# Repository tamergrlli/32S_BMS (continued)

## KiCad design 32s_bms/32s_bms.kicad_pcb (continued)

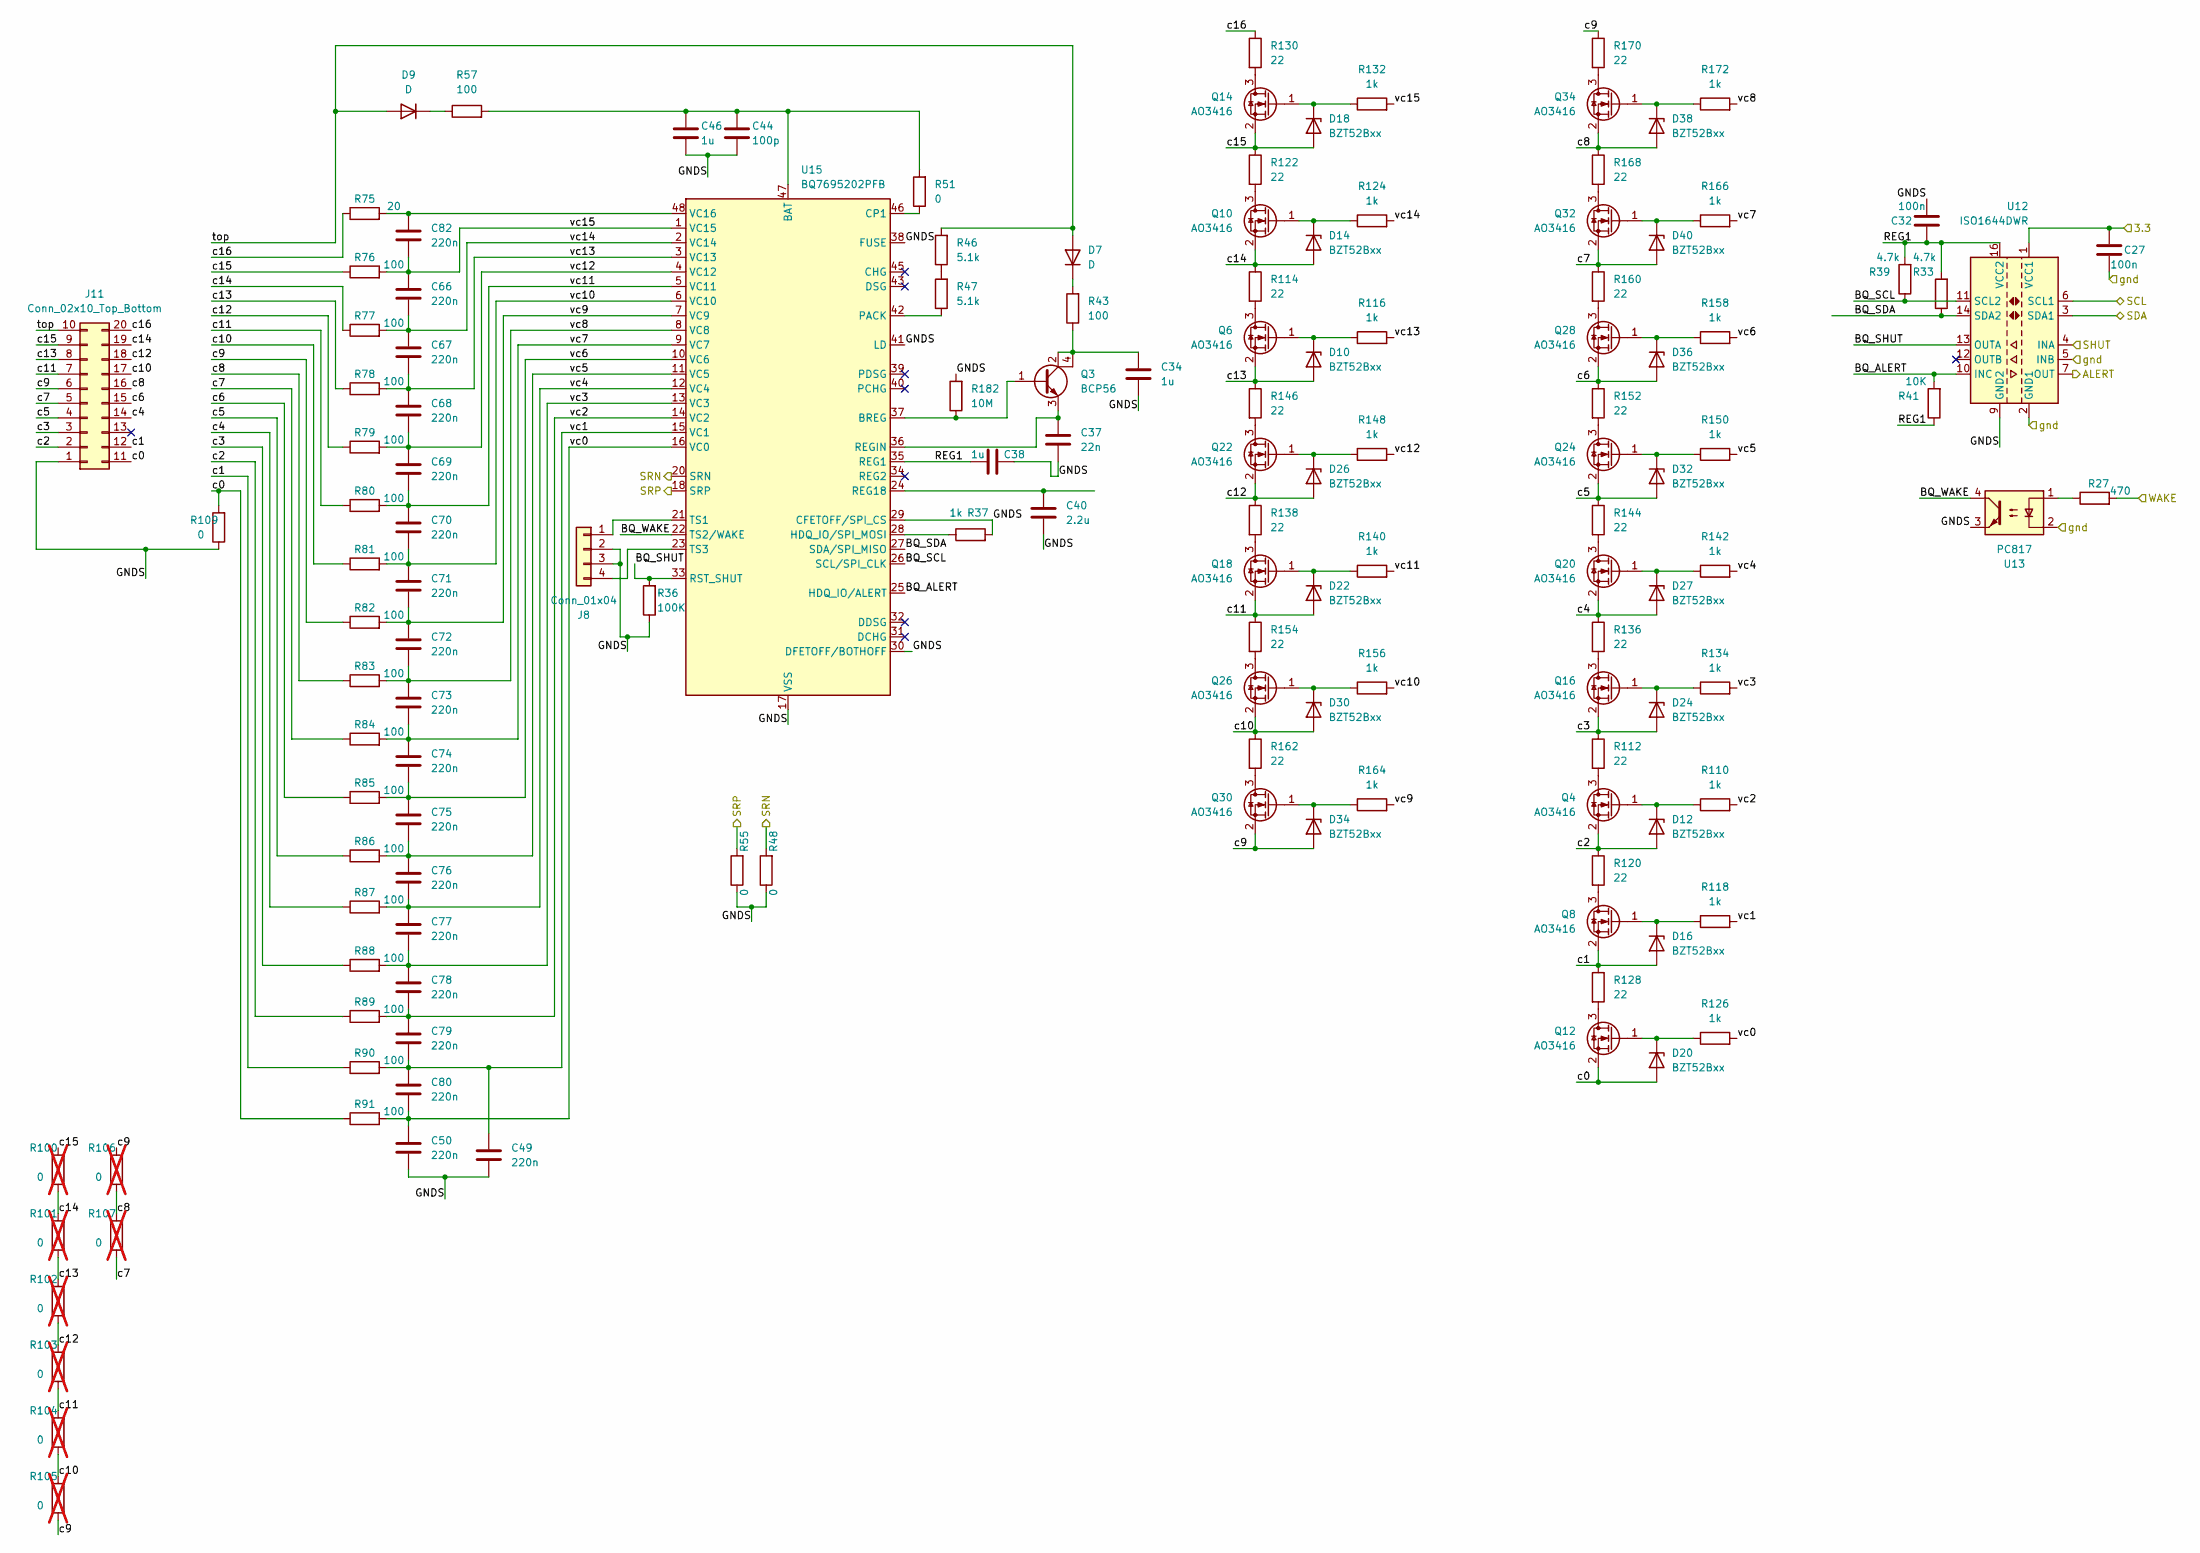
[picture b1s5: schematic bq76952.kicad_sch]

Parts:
C27, C32: 100n; C_0603_1608Metric
C34, C38, C46: 1u; C_0805_2012Metric
C37: 22n; C_0805_2012Metric
C40: 2.2u; C_0805_2012Metric
C44: 100p; C_0603_1608Metric
C49, C50, C66, C67, C68, C69, C70, C71, C72, C73, C74, C75, C76, C77, C78, C79, C80, C82: 220n; C_0603_1608Metric
D7, D9: D; D_SOD-123
D10, D12, D14, D16, D18, D20, D22, D24, D26, D27, D30, D32, D34, D36, D38, D40: BZT52Bxx; D_SOD-123F
J8: Conn_01x04; JST_PH_S4B-PH-SM4-TB_1x04-1MP_P2.00mm_Horizontal
J11: Conn_02x10_Top_Bottom; Molex_Micro-Fit_3.0_43045-2000_2x10_P3.00mm_Horizontal
Q3: BCP56; SOT-223
Q4, Q6, Q8, Q10, Q12, Q14, Q16, Q18, Q20, Q22, Q24, Q26, Q28, Q30, Q32, Q34: AO3416; SOT-23
R27: 470; R_0603_1608Metric
R33, R39: 4.7k; R_0603_1608Metric
R36: 100K; R_0603_1608Metric
R37, R110, R116, R118, R124, R126, R132, R134, R140, R142, R148, R150, R156, R158, R164, R166, R172: 1k; R_0603_1608Metric
R41: 10K; R_0603_1608Metric
R43, R57, R76, R77, R78, R79, R80, R81, R82, R83, R84, R85, R86, R87, R88, R89, R90, R91: 100; R_1206_3216Metric
R46, R47: 5.1k; R_0603_1608Metric
R48, R51, R55, R109: 0; R_0603_1608Metric
R75: 20; R_1206_3216Metric
R100, R101, R102, R103, R104, R105, R106, R107: 0; R_0402_1005Metric; not fitted
R112, R114, R120, R122, R128, R130, R136, R138, R144, R146, R152, R154, R160, R162, R168, R170: 22; R_2512_6332Metric
R182: 10M; R_0603_1608Metric
U12: ISO1644DWR; SOIC-16W_7.5x10.3mm_P1.27mm
U13: PC817; DIP-4_W7.62mm_SMDSocket_SmallPads
U15: BQ7695202PFB; TQFP-48_7x7mm_P0.5mm

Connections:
/IN_OUT/3v3: C27.2, U12.1 (VCC1); also elsewhere on the board
/IN_OUT/gnd: C27.1, U12.2 (GND1), U12.5 (INB), U12.8 (GND1), U13.2; also elsewhere on the board
/MCU/ALERT_BOT: U12.7 (OUT); also elsewhere on the board
/MCU/SCL_BOT: U12.6 (SCL1); also elsewhere on the board
/MCU/SDA_BOT: U12.3 (SDA1); also elsewhere on the board
/MCU/WAKE_BOT: R27.2; also elsewhere on the board
/SHUT: U12.4 (INA); also elsewhere on the board
/bq76952_BOTTOM/BQ_ALERT: R41.2, U12.10 (INC), U15.25 (HDQ_IO/ALERT)
/bq76952_BOTTOM/BQ_SCL: R39.1, U12.11 (SCL2), U15.26 (SCL/SPI_CLK)
/bq76952_BOTTOM/BQ_SDA: R33.1, U12.14 (SDA2), U15.27 (SDA/SPI_MISO)
/bq76952_BOTTOM/BQ_SHUT: R36.2, U12.13 (OUTA), U15.33 (RST_SHUT)
/bq76952_BOTTOM/BQ_WAKE: U13.4, U15.22 (TS2/WAKE)
/bq76952_BOTTOM/GNDS: C32.1, C34.2, C37.2, C38.2, C40.2, C44.2, C46.2, C49.2, C50.2, J8.2, J8.3, J11.1, R36.1, R37.2, R48.1, R55.1, R109.1, R182.2, U12.9 (GND2), U12.15 (GND2), U13.3, U15.17 (VSS), U15.29 (CFETOFF/SPI_CS), U15.30 (DFETOFF/BOTHOFF), U15.38 (FUSE), U15.41 (LD)
/bq76952_BOTTOM/REG1: C32.2, C38.1, R33.2, R39.2, R41.1, U12.16 (VCC2), U15.35 (REG1)
/bq76952_BOTTOM/SRN: R48.2, U15.20 (SRN); also elsewhere on the board
/bq76952_BOTTOM/SRP: R55.2, U15.18 (SRP); also elsewhere on the board
/bq76952_BOTTOM/c0: D20.2 (A), J11.11, Q12.2 (S), R91.1, R109.2
/bq76952_BOTTOM/c1: D16.2 (A), J11.12, Q8.2 (S), R90.1, R128.1
/bq76952_BOTTOM/c2: D12.2 (A), J11.2, Q4.2 (S), R89.1, R120.1
/bq76952_BOTTOM/c3: D24.2 (A), J11.3, Q16.2 (S), R88.1, R112.1
/bq76952_BOTTOM/c4: D27.2 (A), J11.14, Q20.2 (S), R87.1, R136.1
/bq76952_BOTTOM/c5: D32.2 (A), J11.4, Q24.2 (S), R86.1, R144.1
/bq76952_BOTTOM/c6: D36.2 (A), J11.15, Q28.2 (S), R85.1, R152.1
/bq76952_BOTTOM/c7: D40.2 (A), J11.5, Q32.2 (S), R84.1, R107.1, R160.1
/bq76952_BOTTOM/c8: D38.2 (A), J11.16, Q34.2 (S), R83.1, R106.1, R107.2, R168.1
/bq76952_BOTTOM/c9: D34.2 (A), J11.6, Q30.2 (S), R82.1, R105.1, R106.2, R170.1
/bq76952_BOTTOM/c10: D30.2 (A), J11.17, Q26.2 (S), R81.1, R104.1, R105.2, R162.1
/bq76952_BOTTOM/c11: D22.2 (A), J11.7, Q18.2 (S), R80.1, R103.1, R104.2, R154.1
/bq76952_BOTTOM/c12: D26.2 (A), J11.18, Q22.2 (S), R79.1, R102.1, R103.2, R138.1
/bq76952_BOTTOM/c13: D10.2 (A), J11.8, Q6.2 (S), R78.1, R101.1, R102.2, R146.1
/bq76952_BOTTOM/c14: D14.2 (A), J11.19, Q10.2 (S), R77.1, R100.1, R101.2, R114.1
/bq76952_BOTTOM/c15: D18.2 (A), J11.9, Q14.2 (S), R76.1, R100.2, R122.1
/bq76952_BOTTOM/c16: J11.20, R75.1, R130.1
/bq76952_BOTTOM/top: D7.2 (A), D9.2 (A), J11.10, R46.2
/bq76952_BOTTOM/vc0: C50.1, C80.2, R91.2, R126.2, U15.16 (VC0)
/bq76952_BOTTOM/vc1: C49.1, C79.2, C80.1, R90.2, R118.2, U15.15 (VC1)
/bq76952_BOTTOM/vc2: C78.2, C79.1, R89.2, R110.2, U15.14 (VC2)
/bq76952_BOTTOM/vc3: C77.2, C78.1, R88.2, R134.2, U15.13 (VC3)
/bq76952_BOTTOM/vc4: C76.2, C77.1, R87.2, R142.2, U15.12 (VC4)
/bq76952_BOTTOM/vc5: C75.2, C76.1, R86.2, R150.2, U15.11 (VC5)
/bq76952_BOTTOM/vc6: C74.2, C75.1, R85.2, R158.2, U15.10 (VC6)
/bq76952_BOTTOM/vc7: C73.2, C74.1, R84.2, R166.2, U15.9 (VC7)
/bq76952_BOTTOM/vc8: C72.2, C73.1, R83.2, R172.2, U15.8 (VC8)
/bq76952_BOTTOM/vc9: C71.2, C72.1, R82.2, R164.2, U15.7 (VC9)
/bq76952_BOTTOM/vc10: C70.2, C71.1, R81.2, R156.2, U15.6 (VC10)
/bq76952_BOTTOM/vc11: C69.2, C70.1, R80.2, R140.2, U15.5 (VC11)
/bq76952_BOTTOM/vc12: C68.2, C69.1, R79.2, R148.2, U15.4 (VC12)
/bq76952_BOTTOM/vc13: C67.2, C68.1, R78.2, R116.2, U15.3 (VC13)
/bq76952_BOTTOM/vc14: C66.2, C67.1, R77.2, R124.2, U15.2 (VC14)
/bq76952_BOTTOM/vc15: C66.1, C82.2, R76.2, R132.2, U15.1 (VC15)
unnamed: C34.1, Q3.2 (C), Q3.4 (C), R43.1
unnamed: D7.1 (K), R43.2
unnamed: D9.1 (K), R57.1
unnamed: D10.1 (K), Q6.1 (G), R116.1
unnamed: D12.1 (K), Q4.1 (G), R110.1
unnamed: D14.1 (K), Q10.1 (G), R124.1
unnamed: D16.1 (K), Q8.1 (G), R118.1
unnamed: D18.1 (K), Q14.1 (G), R132.1
unnamed: D20.1 (K), Q12.1 (G), R126.1
unnamed: D22.1 (K), Q18.1 (G), R140.1
unnamed: D24.1 (K), Q16.1 (G), R134.1
unnamed: D26.1 (K), Q22.1 (G), R148.1
unnamed: D27.1 (K), Q20.1 (G), R142.1
unnamed: D30.1 (K), Q26.1 (G), R156.1
unnamed: D32.1 (K), Q24.1 (G), R150.1
unnamed: D34.1 (K), Q30.1 (G), R164.1
unnamed: D36.1 (K), Q28.1 (G), R158.1
unnamed: D38.1 (K), Q34.1 (G), R172.1
unnamed: D40.1 (K), Q32.1 (G), R166.1
unnamed: J8.1, U15.21 (TS1)
unnamed: J8.4, U15.23 (TS3)
unnamed: Q3.1 (B), R182.1, U15.37 (BREG)
unnamed: C37.1, Q3.3 (E), U15.36 (REGIN)
unnamed: Q4.3 (D), R112.2
unnamed: Q6.3 (D), R114.2
unnamed: Q8.3 (D), R120.2
unnamed: Q10.3 (D), R122.2
unnamed: Q12.3 (D), R128.2
unnamed: Q14.3 (D), R130.2
unnamed: Q16.3 (D), R136.2
unnamed: Q18.3 (D), R138.2
unnamed: Q20.3 (D), R144.2
unnamed: Q22.3 (D), R146.2
unnamed: Q24.3 (D), R152.2
unnamed: Q26.3 (D), R154.2
unnamed: Q28.3 (D), R160.2
unnamed: Q30.3 (D), R162.2
unnamed: Q32.3 (D), R168.2
unnamed: Q34.3 (D), R170.2
unnamed: R27.1, U13.1
unnamed: R46.1, R47.2
unnamed: C44.1, C46.1, R51.2, R57.2, U15.47 (BAT)
unnamed: R51.1, U15.46 (CP1)
unnamed: R37.1, U15.28 (HDQ_IO/SPI_MOSI)
unnamed: R47.1, U15.42 (PACK)
unnamed: C40.1, U15.24 (REG18)
unnamed: C82.1, R75.2, U15.48 (VC16)

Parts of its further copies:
C26, C31: 100n; C_0603_1608Metric
C33, C36, C45: 1u; C_0805_2012Metric
C35: 22n; C_0805_2012Metric
C39: 2.2u; C_0805_2012Metric
C43: 100p; C_0603_1608Metric
C47, C48, C51, C52, C53, C54, C55, C56, C57, C58, C59, C60, C61, C62, C63, C64, C65, C81: 220n; C_0603_1608Metric
D6, D8: D; D_SOD-123
D11, D13, D15, D17, D19, D21, D23, D25, D28, D29, D31, D33, D35, D37, D39, D41: BZT52Bxx; D_SOD-123F
J7: Conn_01x04; JST_PH_S4B-PH-SM4-TB_1x04-1MP_P2.00mm_Horizontal
J10: Conn_02x10_Top_Bottom; Molex_Micro-Fit_3.0_43045-2000_2x10_P3.00mm_Horizontal
Q2: BCP56; SOT-223
Q5, Q7, Q9, Q11, Q13, Q15, Q17, Q19, Q21, Q23, Q25, Q27, Q29, Q31, Q33, Q35: AO3416; SOT-23
R26: 470; R_0603_1608Metric
R32, R38: 4.7k; R_0603_1608Metric
R34: 100K; R_0603_1608Metric
R35, R111, R117, R119, R125, R127, R133, R135, R141, R143, R149, R151, R157, R159, R165, R167, R173: 1k; R_0603_1608Metric
R40: 10K; R_0603_1608Metric
R42, R56, R59, R60, R61, R62, R63, R64, R65, R66, R67, R68, R69, R70, R71, R72, R73, R74: 100; R_1206_3216Metric
R44, R45: 5.1k; R_0603_1608Metric
R50, R52, R53, R108: 0; R_0603_1608Metric
R58: 20; R_1206_3216Metric
R92, R93, R94, R95, R96, R97, R98, R99: 0; R_0402_1005Metric; not fitted
R113, R115, R121, R123, R129, R131, R137, R139, R145, R147, R153, R155, R161, R163, R169, R171: 22; R_2512_6332Metric
R183: 10M; R_0603_1608Metric
U10: ISO1644DWR; SOIC-16W_7.5x10.3mm_P1.27mm
U11: PC817; DIP-4_W7.62mm_SMDSocket_SmallPads
U14: BQ7695202PFB; TQFP-48_7x7mm_P0.5mm

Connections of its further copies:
/IN_OUT/3v3: C26.2, U10.1 (VCC1); also elsewhere on the board
/IN_OUT/gnd: C26.1, U10.2 (GND1), U10.5 (INB), U10.8 (GND1), U11.2; also elsewhere on the board
/MCU/ALERT_TOP: U10.7 (OUT); also elsewhere on the board
/MCU/SCL_TOP: U10.6 (SCL1); also elsewhere on the board
/MCU/SDA_TOP: U10.3 (SDA1); also elsewhere on the board
/MCU/WAKE_TOP: R26.2; also elsewhere on the board
/SHUT: U10.4 (INA); also elsewhere on the board
/bq76952_TOP/BQ_ALERT: R40.2, U10.10 (INC), U14.25 (HDQ_IO/ALERT)
/bq76952_TOP/BQ_SCL: R38.1, U10.11 (SCL2), U14.26 (SCL/SPI_CLK)
/bq76952_TOP/BQ_SDA: R32.1, U10.14 (SDA2), U14.27 (SDA/SPI_MISO)
/bq76952_TOP/BQ_SHUT: R34.2, U10.13 (OUTA), U14.33 (RST_SHUT)
/bq76952_TOP/BQ_WAKE: U11.4, U14.22 (TS2/WAKE)
/bq76952_TOP/GNDS: C31.1, C33.2, C35.2, C36.2, C39.2, C43.2, C45.2, C47.2, C48.2, J7.2, J7.3, J10.1, R34.1, R35.2, R52.1, R53.1, R108.1, R183.2, U10.9 (GND2), U10.15 (GND2), U11.3, U14.17 (VSS), U14.29 (CFETOFF/SPI_CS), U14.30 (DFETOFF/BOTHOFF), U14.38 (FUSE), U14.41 (LD)
/bq76952_TOP/REG1: C31.2, C36.1, R32.2, R38.2, R40.1, U10.16 (VCC2), U14.35 (REG1)
/bq76952_TOP/SRN: R52.2, U14.20 (SRN)
/bq76952_TOP/SRP: R53.2, U14.18 (SRP)
/bq76952_TOP/c0: D21.2 (A), J10.11, Q13.2 (S), R74.1, R108.2
/bq76952_TOP/c1: D17.2 (A), J10.12, Q9.2 (S), R73.1, R129.1
/bq76952_TOP/c2: D13.2 (A), J10.2, Q5.2 (S), R72.1, R121.1
/bq76952_TOP/c3: D25.2 (A), J10.3, Q17.2 (S), R71.1, R113.1
/bq76952_TOP/c4: D29.2 (A), J10.14, Q21.2 (S), R70.1, R137.1
/bq76952_TOP/c5: D33.2 (A), J10.4, Q25.2 (S), R69.1, R145.1
/bq76952_TOP/c6: D37.2 (A), J10.15, Q29.2 (S), R68.1, R153.1
/bq76952_TOP/c7: D41.2 (A), J10.5, Q33.2 (S), R67.1, R99.1, R161.1
/bq76952_TOP/c8: D39.2 (A), J10.16, Q35.2 (S), R66.1, R98.1, R99.2, R169.1
/bq76952_TOP/c9: D35.2 (A), J10.6, Q31.2 (S), R65.1, R97.1, R98.2, R171.1
/bq76952_TOP/c10: D31.2 (A), J10.17, Q27.2 (S), R64.1, R96.1, R97.2, R163.1
/bq76952_TOP/c11: D23.2 (A), J10.7, Q19.2 (S), R63.1, R95.1, R96.2, R155.1
/bq76952_TOP/c12: D28.2 (A), J10.18, Q23.2 (S), R62.1, R94.1, R95.2, R139.1
/bq76952_TOP/c13: D11.2 (A), J10.8, Q7.2 (S), R61.1, R93.1, R94.2, R147.1
/bq76952_TOP/c14: D15.2 (A), J10.19, Q11.2 (S), R60.1, R92.1, R93.2, R115.1
/bq76952_TOP/c15: D19.2 (A), J10.9, Q15.2 (S), R59.1, R92.2, R123.1
/bq76952_TOP/c16: J10.20, R58.1, R131.1
/bq76952_TOP/top: D6.2 (A), D8.2 (A), J10.10, R44.2
/bq76952_TOP/vc0: C48.1, C65.2, R74.2, R127.2, U14.16 (VC0)
/bq76952_TOP/vc1: C47.1, C64.2, C65.1, R73.2, R119.2, U14.15 (VC1)
/bq76952_TOP/vc2: C63.2, C64.1, R72.2, R111.2, U14.14 (VC2)
/bq76952_TOP/vc3: C62.2, C63.1, R71.2, R135.2, U14.13 (VC3)
/bq76952_TOP/vc4: C61.2, C62.1, R70.2, R143.2, U14.12 (VC4)
/bq76952_TOP/vc5: C60.2, C61.1, R69.2, R151.2, U14.11 (VC5)
/bq76952_TOP/vc6: C59.2, C60.1, R68.2, R159.2, U14.10 (VC6)
/bq76952_TOP/vc7: C58.2, C59.1, R67.2, R167.2, U14.9 (VC7)
/bq76952_TOP/vc8: C57.2, C58.1, R66.2, R173.2, U14.8 (VC8)
/bq76952_TOP/vc9: C56.2, C57.1, R65.2, R165.2, U14.7 (VC9)
/bq76952_TOP/vc10: C55.2, C56.1, R64.2, R157.2, U14.6 (VC10)
/bq76952_TOP/vc11: C54.2, C55.1, R63.2, R141.2, U14.5 (VC11)
/bq76952_TOP/vc12: C53.2, C54.1, R62.2, R149.2, U14.4 (VC12)
/bq76952_TOP/vc13: C52.2, C53.1, R61.2, R117.2, U14.3 (VC13)
/bq76952_TOP/vc14: C51.2, C52.1, R60.2, R125.2, U14.2 (VC14)
/bq76952_TOP/vc15: C51.1, C81.2, R59.2, R133.2, U14.1 (VC15)
unnamed: C33.1, Q2.2 (C), Q2.4 (C), R42.1
unnamed: D6.1 (K), R42.2
unnamed: D8.1 (K), R56.1
unnamed: D11.1 (K), Q7.1 (G), R117.1
unnamed: D13.1 (K), Q5.1 (G), R111.1
unnamed: D15.1 (K), Q11.1 (G), R125.1
unnamed: D17.1 (K), Q9.1 (G), R119.1
unnamed: D19.1 (K), Q15.1 (G), R133.1
unnamed: D21.1 (K), Q13.1 (G), R127.1
unnamed: D23.1 (K), Q19.1 (G), R141.1
unnamed: D25.1 (K), Q17.1 (G), R135.1
unnamed: D28.1 (K), Q23.1 (G), R149.1
unnamed: D29.1 (K), Q21.1 (G), R143.1
unnamed: D31.1 (K), Q27.1 (G), R157.1
unnamed: D33.1 (K), Q25.1 (G), R151.1
unnamed: D35.1 (K), Q31.1 (G), R165.1
unnamed: D37.1 (K), Q29.1 (G), R159.1
unnamed: D39.1 (K), Q35.1 (G), R173.1
unnamed: D41.1 (K), Q33.1 (G), R167.1
unnamed: J7.1, U14.21 (TS1)
unnamed: J7.4, U14.23 (TS3)
unnamed: Q2.1 (B), R183.1, U14.37 (BREG)
unnamed: C35.1, Q2.3 (E), U14.36 (REGIN)
unnamed: Q5.3 (D), R113.2
unnamed: Q7.3 (D), R115.2
unnamed: Q9.3 (D), R121.2
unnamed: Q11.3 (D), R123.2
unnamed: Q13.3 (D), R129.2
unnamed: Q15.3 (D), R131.2
unnamed: Q17.3 (D), R137.2
unnamed: Q19.3 (D), R139.2
unnamed: Q21.3 (D), R145.2
unnamed: Q23.3 (D), R147.2
unnamed: Q25.3 (D), R153.2
unnamed: Q27.3 (D), R155.2
unnamed: Q29.3 (D), R161.2
unnamed: Q31.3 (D), R163.2
unnamed: Q33.3 (D), R169.2
unnamed: Q35.3 (D), R171.2
unnamed: R26.1, U11.1
unnamed: R44.1, R45.2
unnamed: C43.1, C45.1, R50.2, R56.2, U14.47 (BAT)
unnamed: R50.1, U14.46 (CP1)
unnamed: R35.1, U14.28 (HDQ_IO/SPI_MOSI)
unnamed: R45.1, U14.42 (PACK)
unnamed: C39.1, U14.24 (REG18)
unnamed: C81.1, R58.2, U14.48 (VC16)

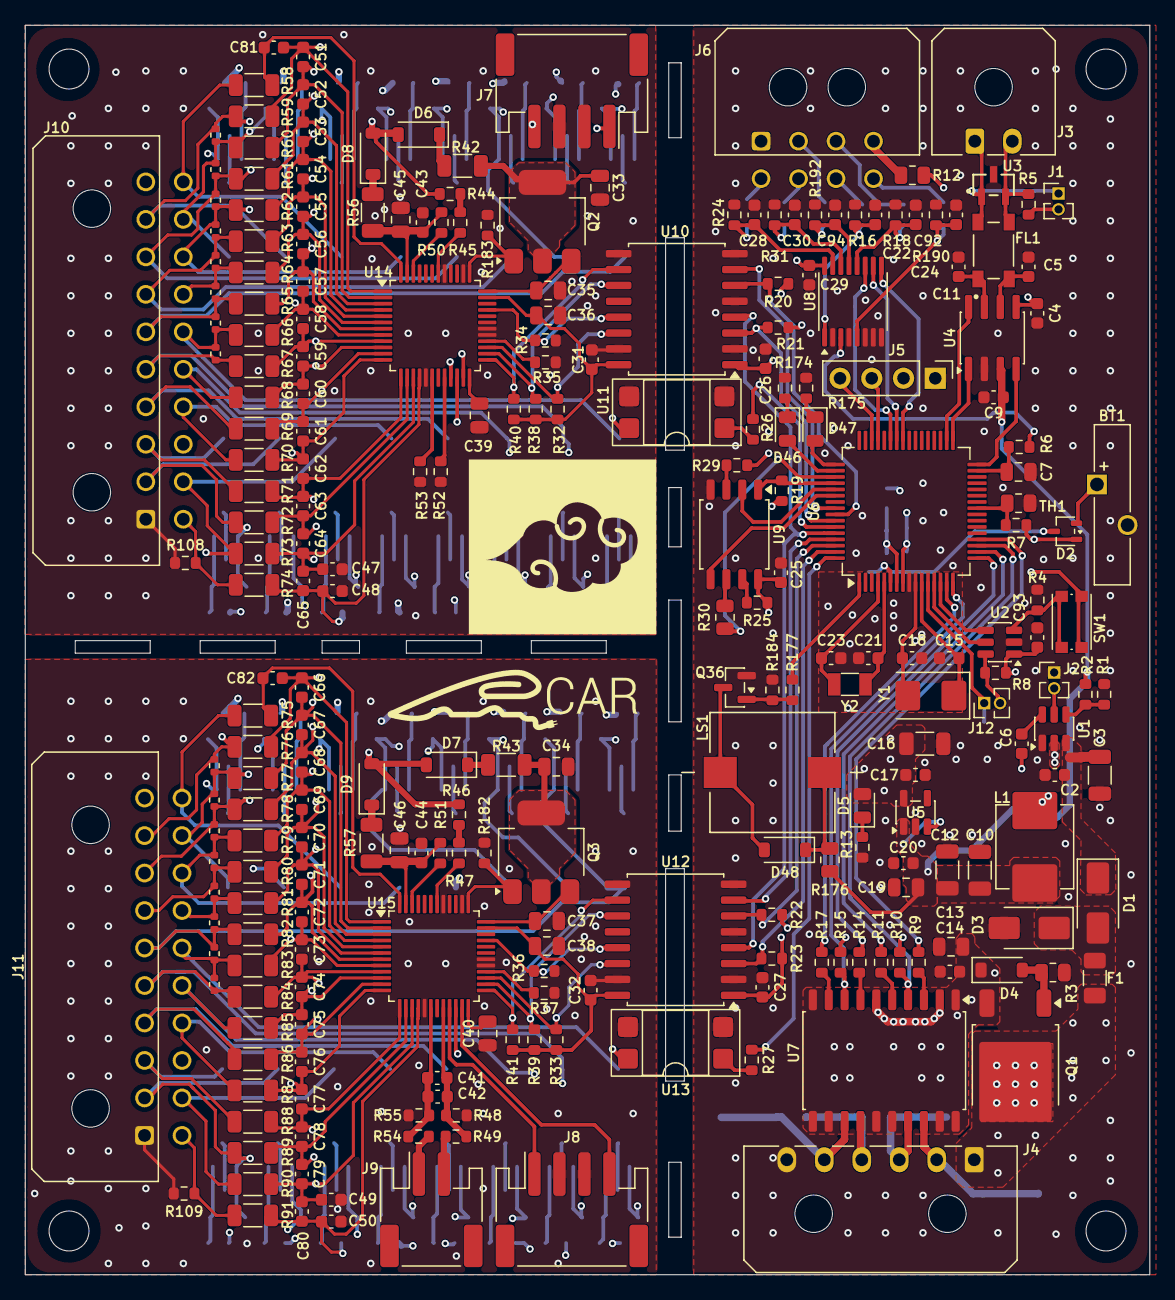
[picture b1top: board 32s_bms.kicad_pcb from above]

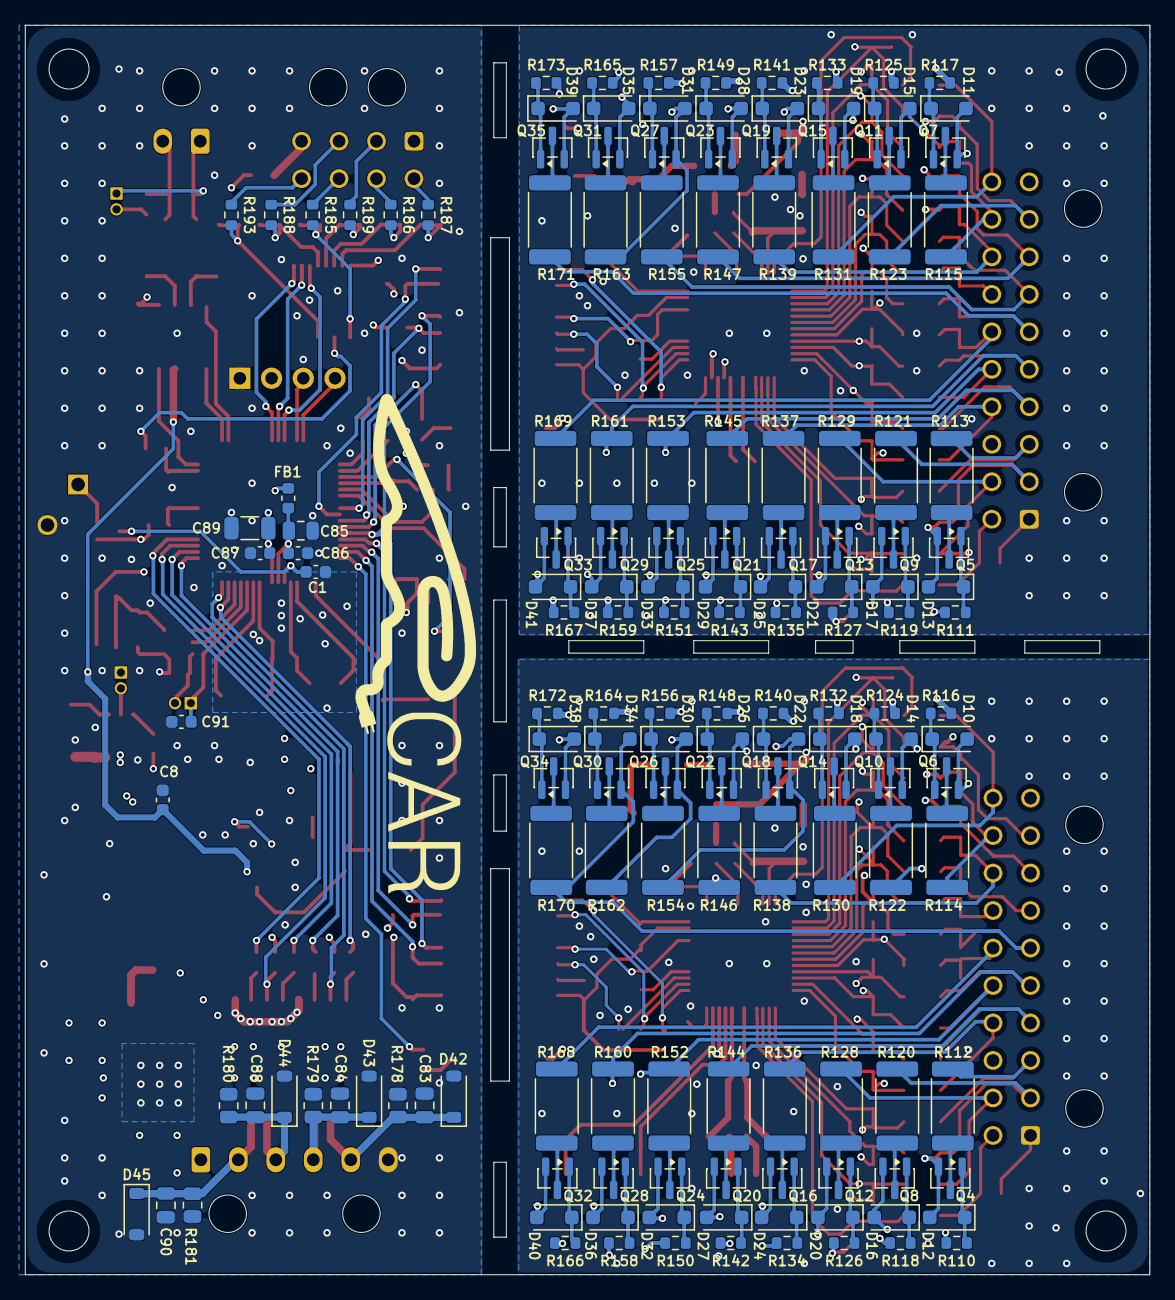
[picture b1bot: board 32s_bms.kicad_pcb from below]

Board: 4 copper layers, 90.0 x 100.0 mm, 410 parts (154 on the bottom side), 274 nets.
